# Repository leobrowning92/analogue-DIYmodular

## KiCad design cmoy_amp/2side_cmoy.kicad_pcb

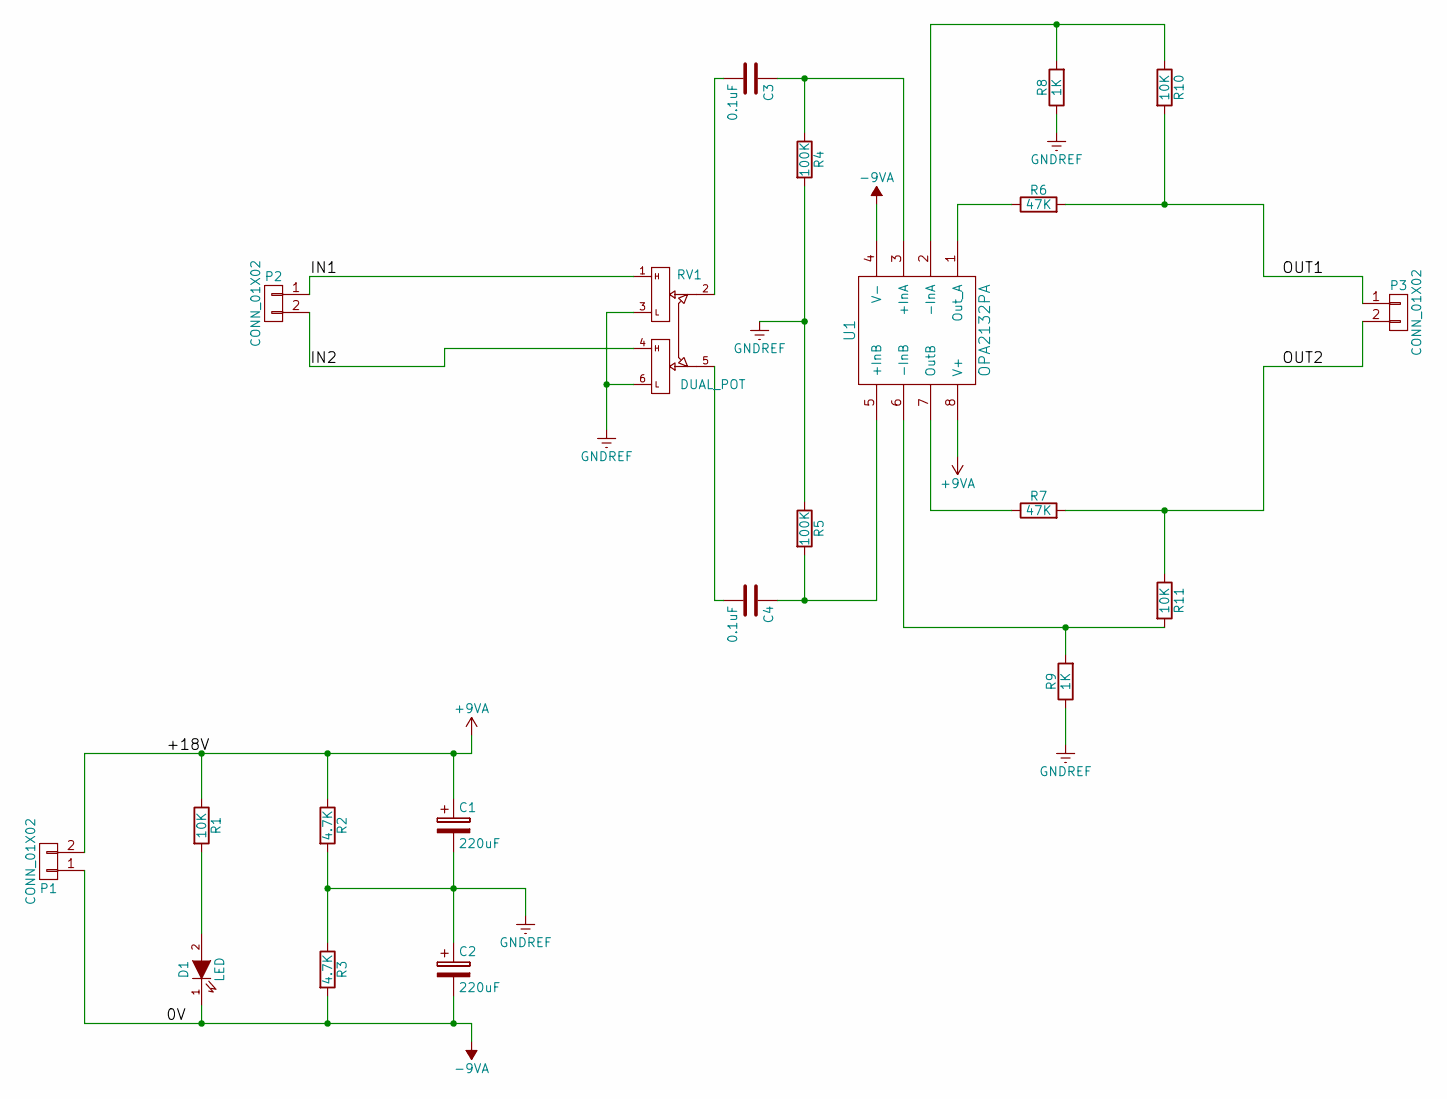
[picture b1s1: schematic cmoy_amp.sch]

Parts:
C1, C2: 220uF; C_Radial_D10_L16_P5
C3, C4: 0.1uF; C_Rect_L7_W6_P5
D1: LED; LED-5MM
P1, P2, P3: CONN_01X02; Pin_Header_Straight_1x02
R1, R10, R11: 10K; Resistor_Horizontal_RM10mm
R2, R3: 4.7K; Resistor_Horizontal_RM10mm
R4, R5: 100K; Resistor_Horizontal_RM10mm
R6, R7: 47K; Resistor_Horizontal_RM10mm
R8, R9: 1K; Resistor_Horizontal_RM10mm
RV1: DUAL_POT; Potentiometer_BOURNS_PD902_dual
U1: OPA2132PA; DIP-8_W7.62mm_LongPads

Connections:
+9VA: C1.1, P1.2, R1.1, R2.1, U1.8 (V+)
-9VA: C2.2, D1.1 (K), P1.1, R3.2, U1.4 (V-)
/IN1: P2.1, RV1.1
/IN2: P2.2, RV1.4
/OUT1: P3.1, R6.2, R10.2
/OUT2: P3.2, R7.2, R11.1
GNDREF: C1.2, C2.1, R2.2, R3.1, R4.2, R5.1, R8.1, R9.1, RV1.3, RV1.6
unnamed: C3.1, R4.1, U1.3 (+InA)
unnamed: C3.2, RV1.2
unnamed: C4.1, R5.2, U1.5 (+InB)
unnamed: C4.2, RV1.5
unnamed: D1.2 (A), R1.2
unnamed: R6.1, U1.1 (Out_A)
unnamed: R7.1, U1.7 (OutB)
unnamed: R8.2, R10.1, U1.2 (-InA)
unnamed: R9.2, R11.2, U1.6 (-InB)

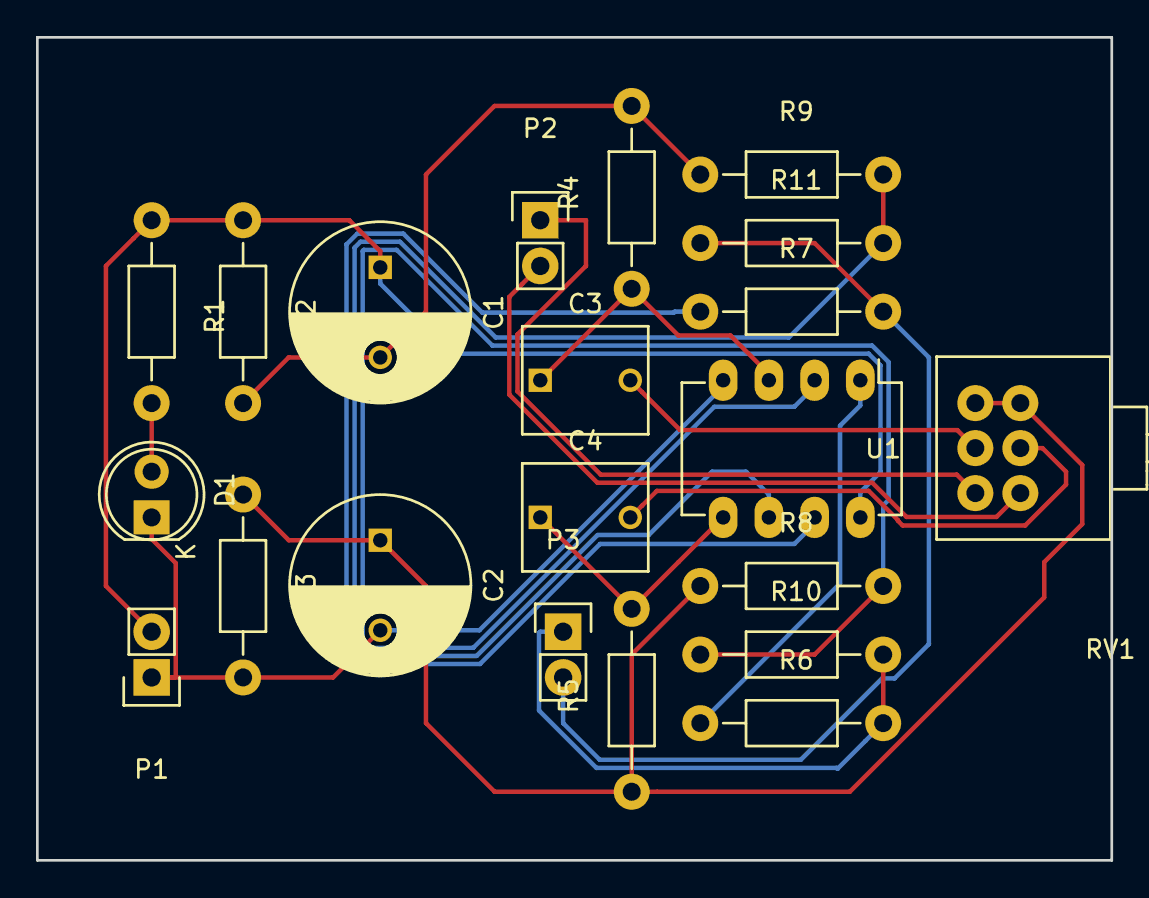
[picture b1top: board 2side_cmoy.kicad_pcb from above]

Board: 2 copper layers, 59.7 x 45.7 mm, 21 parts (0 on the bottom side), 16 nets.

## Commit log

2017-04-11 added cmoy amp
2017-10-15 added mono lm386 amp schematic
2017-10-19 cleaning up project folder
